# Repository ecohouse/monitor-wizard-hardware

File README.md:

# monitor-wizard-hardware
Schematic and board layout for the Monitor Wizard hardware.

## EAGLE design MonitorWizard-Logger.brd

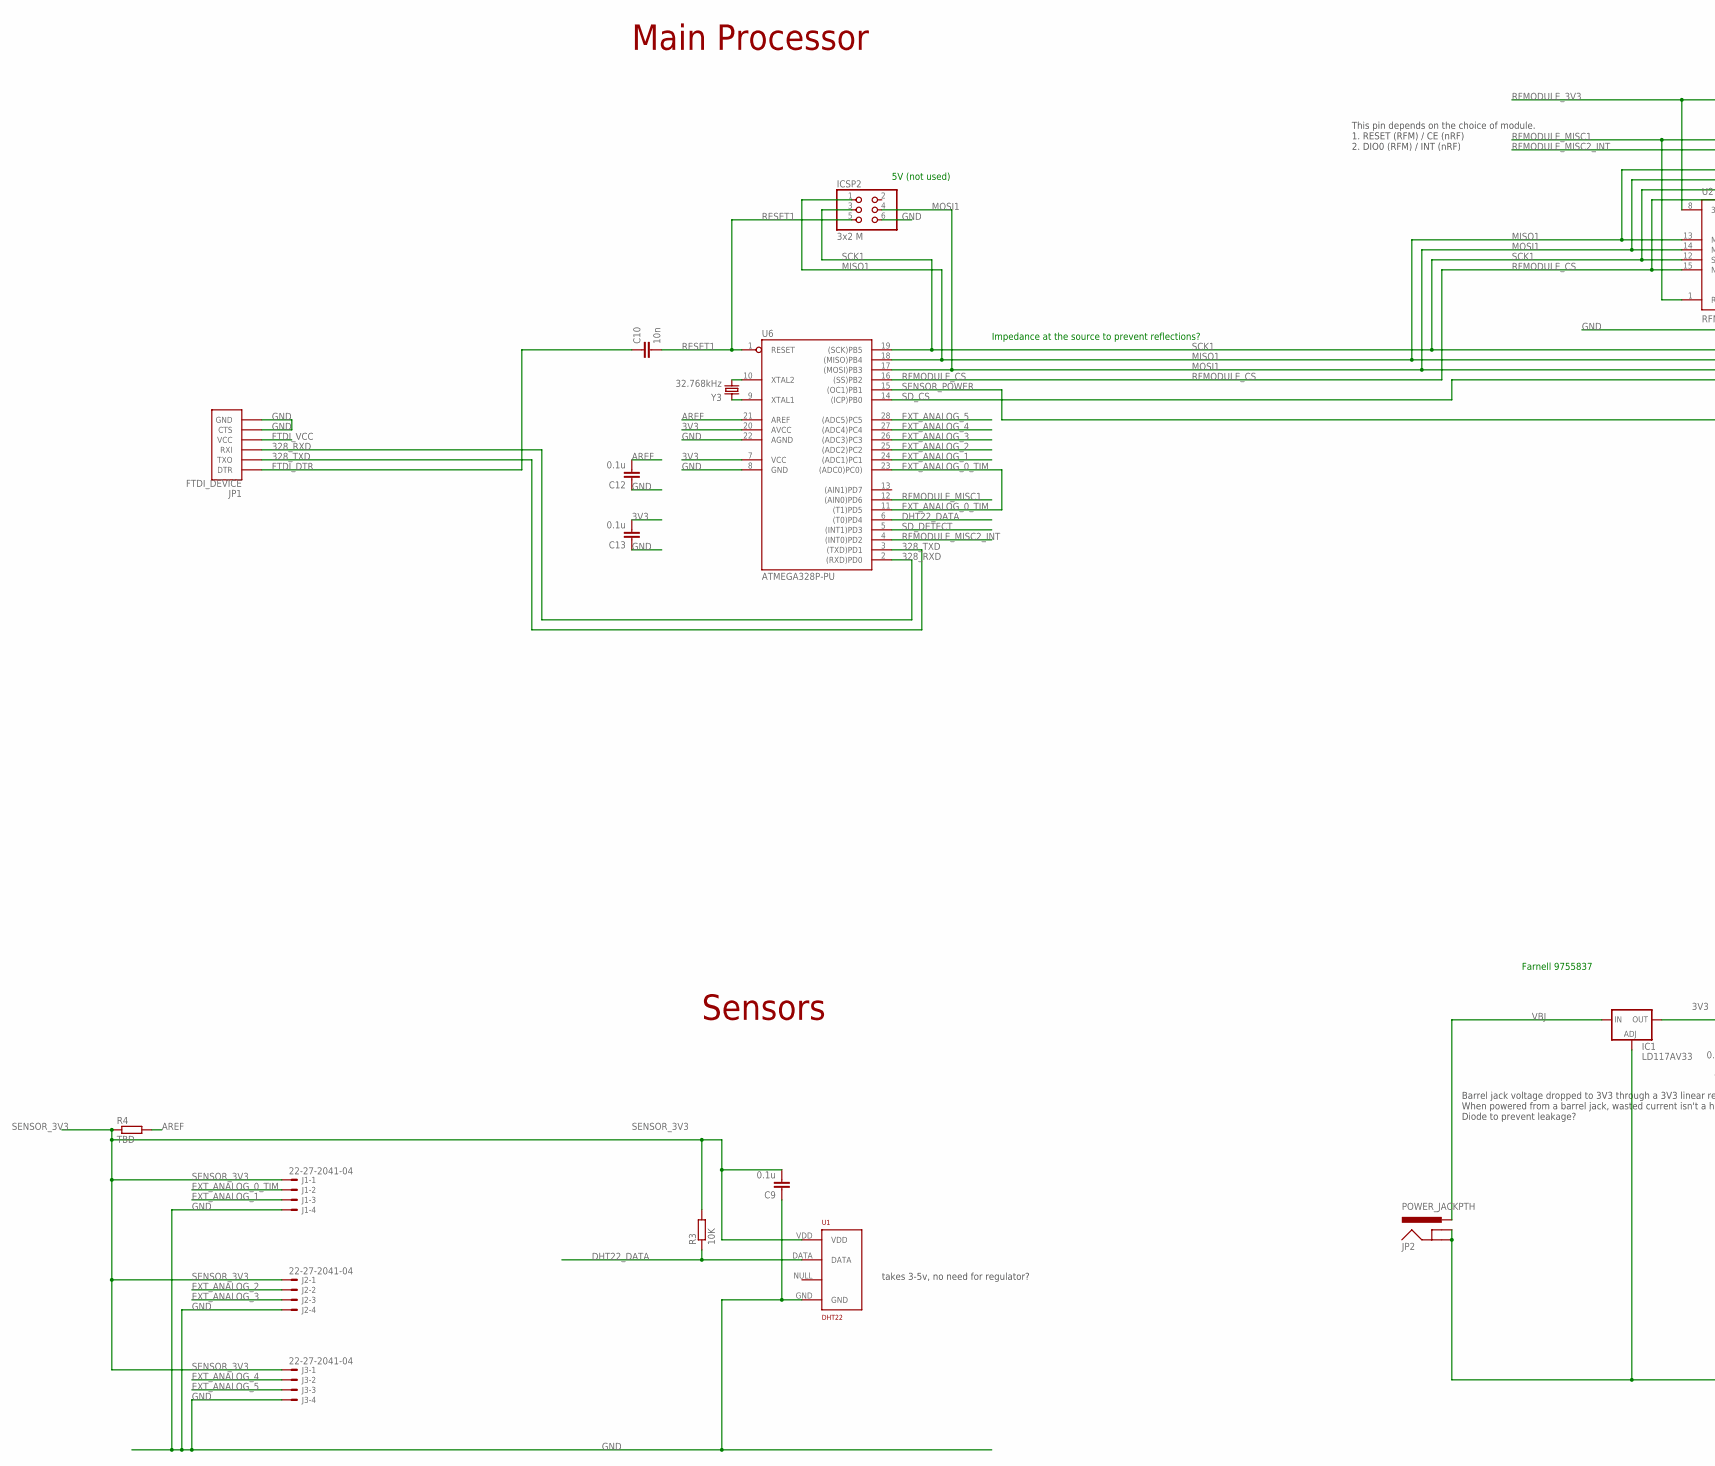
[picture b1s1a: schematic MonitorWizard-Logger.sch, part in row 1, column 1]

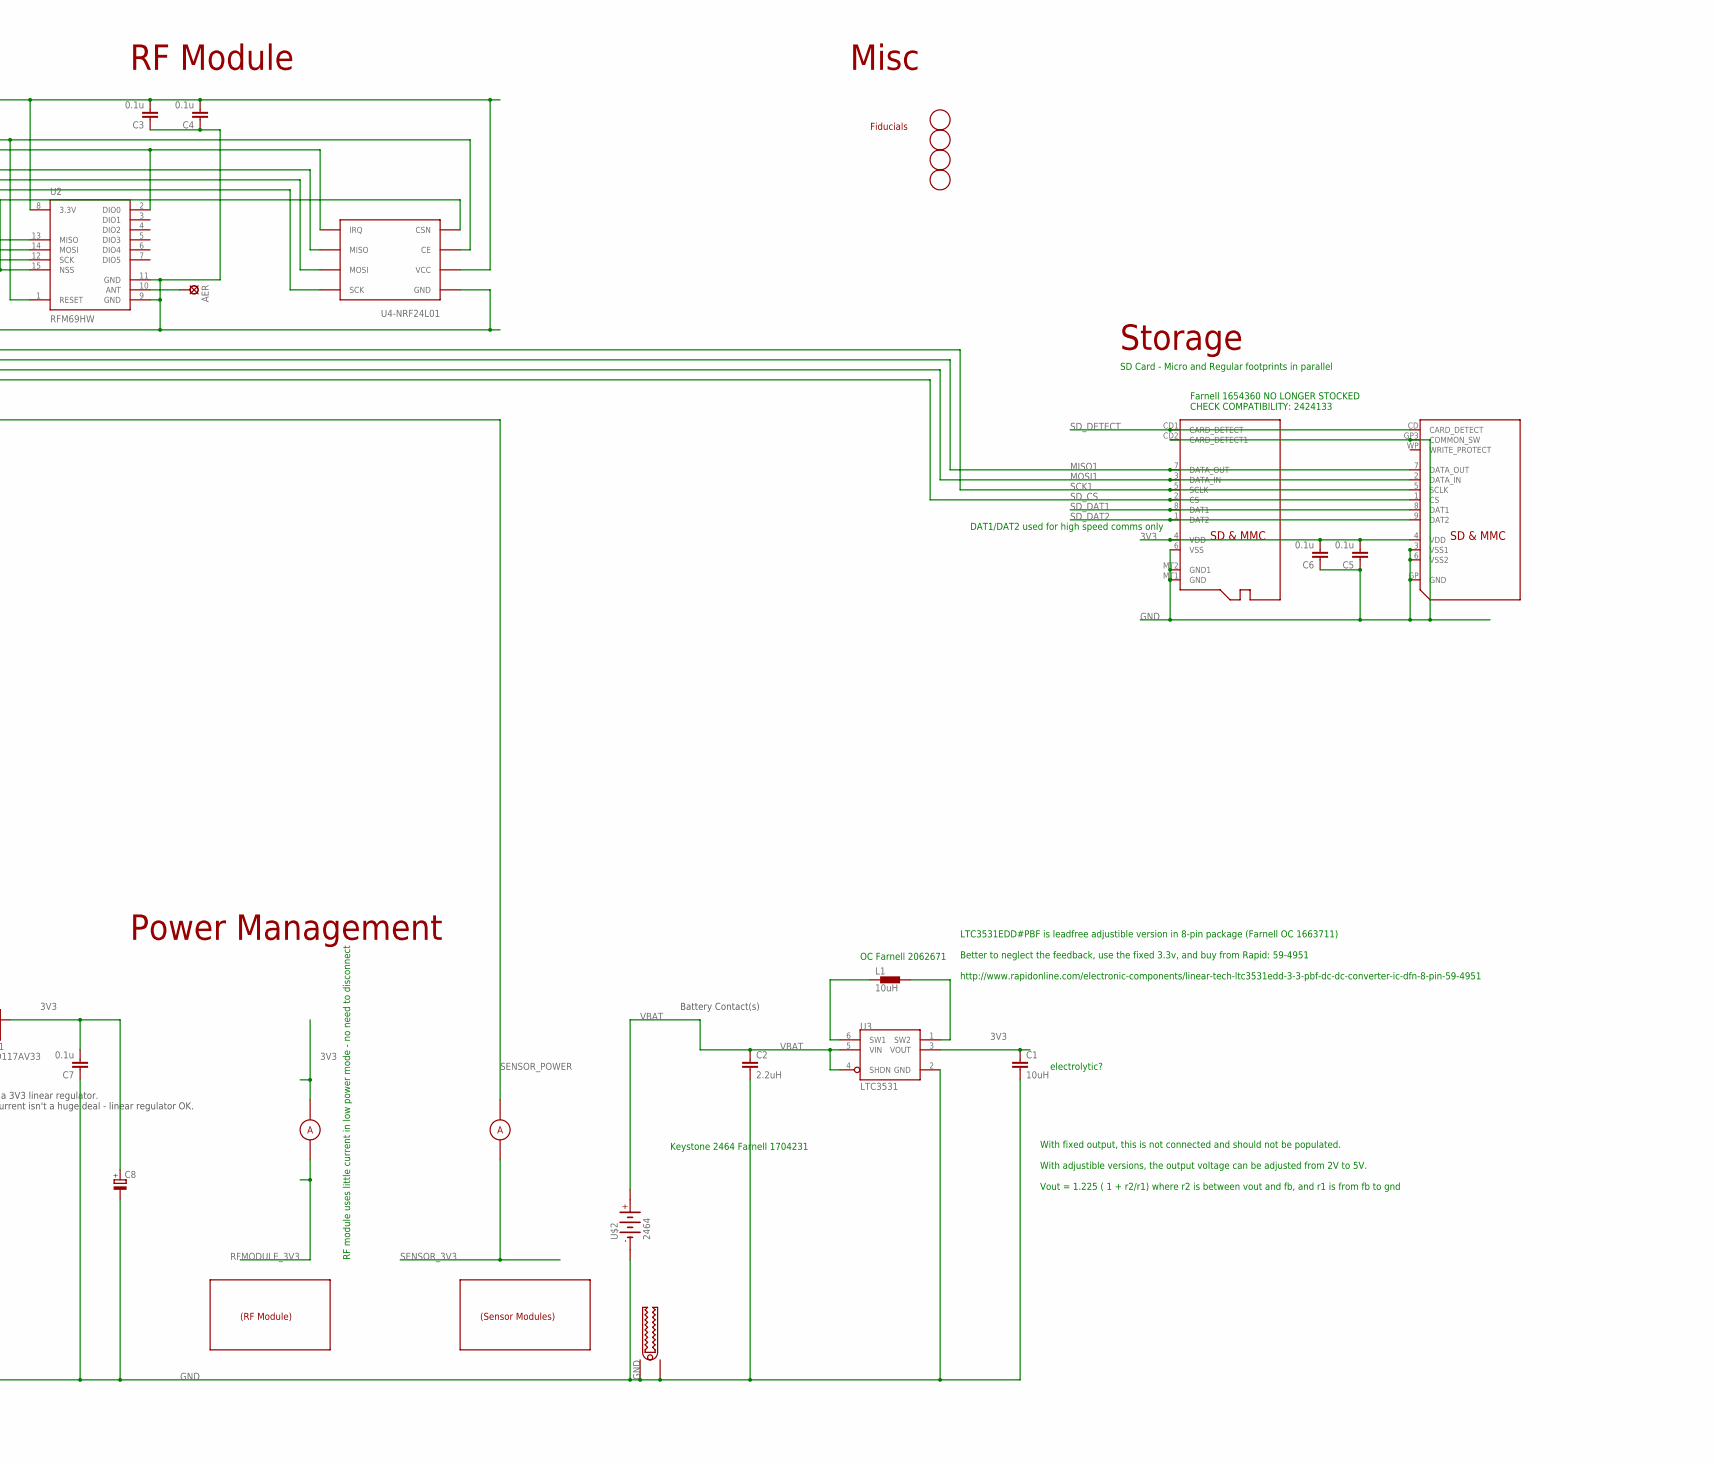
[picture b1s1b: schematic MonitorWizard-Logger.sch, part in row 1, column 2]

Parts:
AER: LSP10
C1: 10uH; C025-024X044
C2: 2.2uH; C025-024X044
C3, C4, C5, C6, C7, C9, C12, C13: 0.1u; C025-024X044
C8: CPOL-EUE2.5-6; E2,5-6
C10: 10n; C025-024X044
CON1: MICROSD
FD1, FD2, FD3, FD4: FIDUCIALMOUNT; FIDUCIA-MOUNT
GND: ALLIGATOR
IC1: LD117AV33; TO220L1
ICSP2: 3x2 M; 2X03
I_RF: CURRENT_MEASURE_0.4A; CURRENT_MEASURE
I_SENSE: CURRENT_MEASURE_0.4A; CURRENT_MEASURE
J1, J2, J3: 22-27-2041-04; 6410-04
JP1: FTDI_DEVICE; FTDI_DEVICE_SIDE
JP2: POWER_JACKPTH; POWER_JACK_PTH
L1: 10uH; L-RADIAL-2-5OD
R3: 10K; 0207/10
R4: TBD; 0207/10
U1: DHT22; RHT03_DHT-22
U2: RFM69HW; RFM69W-XXXS2
U3: LTC3531; TSOT23-6
U4-NRF24L01: NRF24L01+-PCB-AERIAL; NRF24L01-PCB-AERIAL
U6: ATMEGA328P-PU; DIL28-3
U$1: SDMMC06132; 06132
U$2: 2464
Y3: 32.768kHz; TC26HEZ

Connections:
3V3: C1.1, C5.2, C6.2, C7.2, C8.+, C13.2, CON1.4 (VDD), IC1.2 (OUT), I_RF.P$1, U3.3 (VOUT), U6.7 (VCC), U6.20 (AVCC), U$1.4 (VDD)
328_RXD: JP1.P$3 (RXI), U6.2 ((RXD)PD0)
328_TXD: JP1.P$2 (TXO), U6.3 ((TXD)PD1)
AREF: C12.2, R4.2, U6.21 (AREF)
DHT22_DATA: R3.1, U1.DATA, U6.6 ((T0)PD4)
EXT_ANALOG_0_TIM: J1.2, U6.11 ((T1)PD5), U6.23 ((ADC0)PC0))
EXT_ANALOG_1: J1.3, U6.24 ((ADC1)PC1)
EXT_ANALOG_2: J2.2, U6.25 ((ADC2)PC2)
EXT_ANALOG_3: J2.3, U6.26 ((ADC3)PC3)
EXT_ANALOG_4: J3.2, U6.27 ((ADC4)PC4)
EXT_ANALOG_5: J3.3, U6.28 ((ADC5)PC5)
FTDI_DTR: C10.1, JP1.P$1 (DTR)
FTDI_VCC: JP1.P$4 (VCC)
GND: C1.2, C2.2, C3.1, C4.1, C5.1, C6.1, C7.1, C8.-, C9.1, C12.1, C13.1, CON1.6 (VSS), CON1.CD2 (CARD_DETECT1), CON1.MT1 (GND), CON1.MT2 (GND1), GND.BTM, GND.TOP, IC1.1 (ADJ), ICSP2.6, J1.4, J2.4, J3.4, JP1.P$5 (CTS), JP1.P$6 (GND), JP2.GND, JP2.GNDBREAK, U1.GND, U2.9 (GND), U2.11 (GND), U3.2 (GND), U4-NRF24L01.P$1 (GND), U6.8 (GND), U6.22 (AGND), U$1.3 (VSS1), U$1.6 (VSS2), U$1.GP (GND), U$1.GP3 (COMMON_SW), U$2.-
MISO1: CON1.7 (DATA_OUT), ICSP2.1, U2.13 (MISO), U4-NRF24L01.P$7 (MISO), U6.18 ((MISO)PB4), U$1.7 (DATA_OUT)
MOSI1: CON1.3 (DATA_IN), ICSP2.4, U2.14 (MOSI), U4-NRF24L01.P$6 (MOSI), U6.17 ((MOSI)PB3), U$1.2 (DATA_IN)
unnamed: L1.P$2 (2), U3.1 (SW2)
unnamed: L1.P$1 (1), U3.6 (SW1)
unnamed: AER.MP, U2.10 (ANT)
RESET1: C10.2, ICSP2.5, U6.1 (RESET)
RFMODULE_3V3: C3.2, C4.2, I_RF.P$2, U2.8 (3.3V), U4-NRF24L01.P$2 (VCC)
RFMODULE_CS: U2.15 (NSS), U4-NRF24L01.P$4 (CSN), U6.16 ((SS)PB2)
RFMODULE_MISC1: U2.1 (RESET), U4-NRF24L01.P$3 (CE), U6.12 ((AIN0)PD6)
RFMODULE_MISC2_INT: U2.2 (DIO0), U4-NRF24L01.P$8 (IRQ), U6.4 ((INT0)PD2)
SCK1: CON1.5 (SCLK), ICSP2.3, U2.12 (SCK), U4-NRF24L01.P$5 (SCK), U6.19 ((SCK)PB5), U$1.5 (SCLK)
SD_CS: CON1.2 (CS), U6.14 ((ICP)PB0), U$1.1 (CS)
SD_DAT1: CON1.8 (DAT1), U$1.8 (DAT1)
SD_DAT2: CON1.1 (DAT2), U$1.9 (DAT2)
SD_DETECT: CON1.CD1 (CARD_DETECT), U6.5 ((INT1)PD3), U$1.CD (CARD_DETECT)
SENSOR_3V3: C9.2, I_SENSE.P$2, J1.1, J2.1, J3.1, R3.2, R4.1, U1.VDD
SENSOR_POWER: I_SENSE.P$1, U6.15 ((OC1)PB1)
VBAT: C2.1, U3.4 (SHDN), U3.5 (VIN), U$2.+
VBJ: IC1.3 (IN), JP2.PWR
XTAL_N: U6.9 (XTAL1), Y3.2
XTAL_P: U6.10 (XTAL2), Y3.1

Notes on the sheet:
RF Module
Main Processor
Sensors
Power Management
This pin depends on the choice of module. 1. RESET (RFM) / CE (nRF) 2. DIO0 (RFM) / INT (nRF)
Barrel jack voltage dropped to 3V3 through a 3V3 linear regulator. When powered from a barrel jack, wasted current isn't a huge deal - linear regulator OK. Diode to prevent leakage?
Misc
(RF Module)
(Sensor Modules)
Battery Contact(s)
Fiducials
takes 3-5v, no need for regulator?
LTC3531EDD#PBF is leadfree adjustible version in 8-pin package (Farnell OC 1663711) Better to neglect the feedback, use the fixed 3.3v, and buy from Rapid: 59-4951 http://www.rapidonline.com/electronic-components/linear-tech-ltc3531edd-3-3-pbf-dc-dc-converter-ic-dfn-8-pin-59-4951
With fixed output, this is not connected and should not be populated. With adjustible versions, the output voltage can be adjusted from 2V to 5V. Vout = 1.225 ( 1 + r2/r1) where r2 is between vout and fb, and r1 is from fb to gnd
OC Farnell 2062671
electrolytic?
Farnell 9755837
SD Card - Micro and Regular footprints in parallel
Storage
Farnell 1654360 NO LONGER STOCKED CHECK COMPATIBILITY: 2424133
Keystone 2464 Farnell 1704231
RF module uses little current in low power mode - no need to disconnect
DAT1/DAT2 used for high speed comms only
5V (not used)
Impedance at the source to prevent reflections?

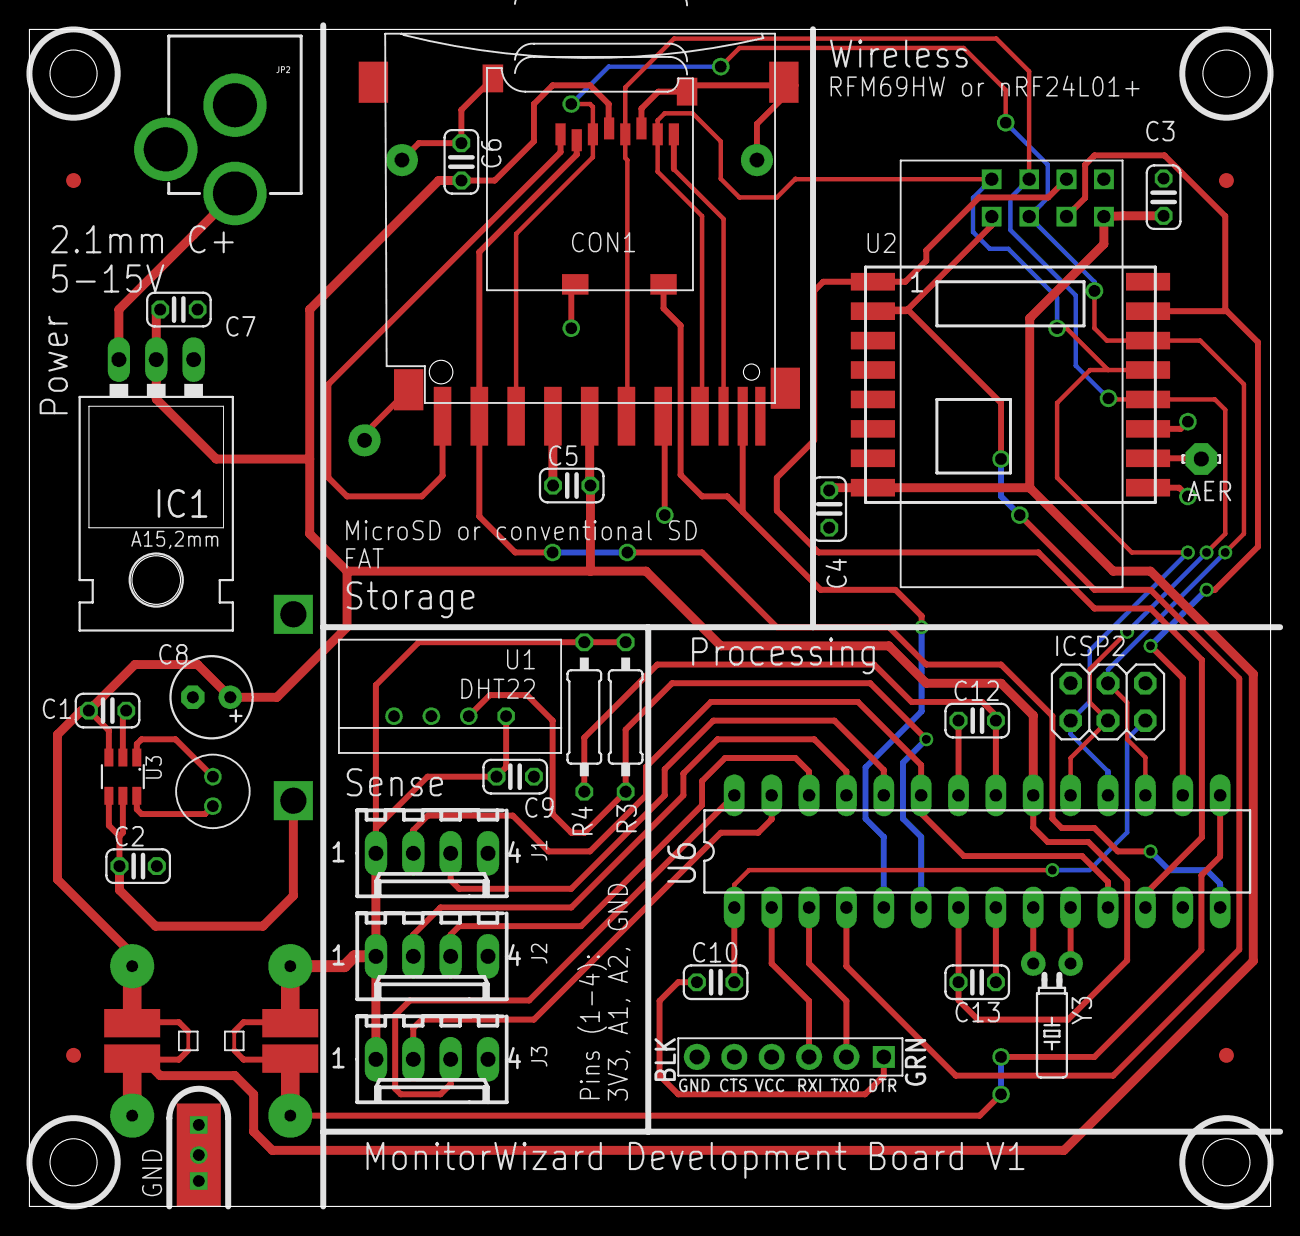
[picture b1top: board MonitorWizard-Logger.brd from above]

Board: 2 copper layers, 84.4 x 80.0 mm, 39 parts (1 on the bottom side), 34 nets.

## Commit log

2015-04-18 Initial commit - not yet complete, but overall design is basically correct.
2015-04-18 Switch to PNP transistors, connect data lines to chip.
2015-04-19 Remove redundant components, play with board layout.
2015-04-30 Add DHT22 library, tweak board layout. Still unfinished.
2015-05-14 Replace power supply with low power switching setup. Remove resistors for level shifting, since everything will now be running at 3.3v.
2015-06-11 Add SD card, battery box. Nearly finished - just have to connect SD and lay out.
2015-06-14 Hopefully completed the schematic.
2015-06-14 Fiddle with layout slightly.
2015-06-14 Update battery box footprint.
2015-06-16 Add decoupling capacitors, begin to route board.
2015-06-19 Route most of layout - just have to route (and terminate?) the SPI bus now.
2015-07-01 Route remaining wires. Still needs the following: Confirm SD card current draw (idle, writing) - is a FET required to power the SD card down? Impedance matching SPI lines / SPI routing improvements? 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
2015-07-01 Fix some DRC errors, tidy silkscreen, improve grounding.
2015-07-01 More silkscreen fixes, move power jack to make more room for screw, tweak spacing of sensor connectors.
2015-07-01 Add electrolytic filter capacitor.
2015-10-12 Make the board smaller by pushing battery box to rear
2015-10-19 Shrink board, move barrel jack out of way of screw head
2015-10-23 Change to a better barrel jack footprint
2015-11-30 Change footprint for LTC3531
2015-12-05 Move some stuff around, add a filter capacitor. As ordered from Screenbond

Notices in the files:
parts and their libraries:
SparkFun-FreqCtrl: Licensing: CC v3.0 Share-Alike You are welcome to use this library for commercial purposes.
SparkFun-RF: Licensing: Creative Commons ShareAlike 4.0 International - https://creativecommons.org/licenses/by-sa/4.0
